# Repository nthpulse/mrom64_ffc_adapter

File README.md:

Adapter board that allows an FFC cable to be used with the MROM64 pin header

See https://nthpulse.net/projects/mrom64_selector_panel/

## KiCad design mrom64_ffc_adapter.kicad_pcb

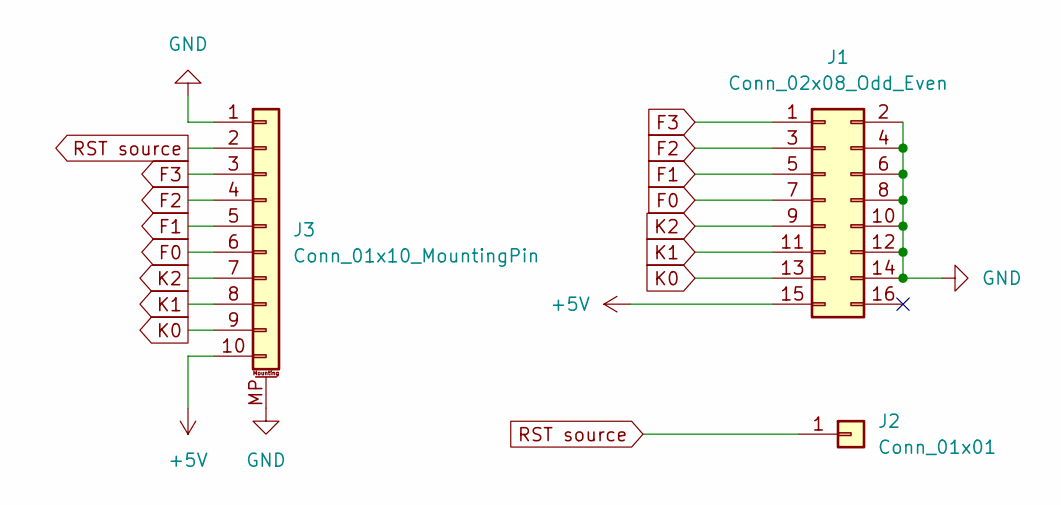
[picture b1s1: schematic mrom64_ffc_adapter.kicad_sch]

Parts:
J1: Conn_02x08_Odd_Even; PinSocket_2x08_P2.54mm_Vertical
J2: Conn_01x01; PinHeader_1x01_P2.54mm_Vertical
J3: Conn_01x10_MountingPin; TE_1-84952-0_1x10-1MP_P1.0mm_Horizontal

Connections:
+5V: J1.15, J3.10
F0: J1.7, J3.6
F1: J1.5, J3.5
F2: J1.3, J3.4
F3: J1.1, J3.3
GND: J1.2, J1.4, J1.6, J1.8, J1.10, J1.12, J1.14, J3.1, J3.MP (MountPin)
K0: J1.13, J3.9
K1: J1.11, J3.8
K2: J1.9, J3.7
RST source: J2.1, J3.2

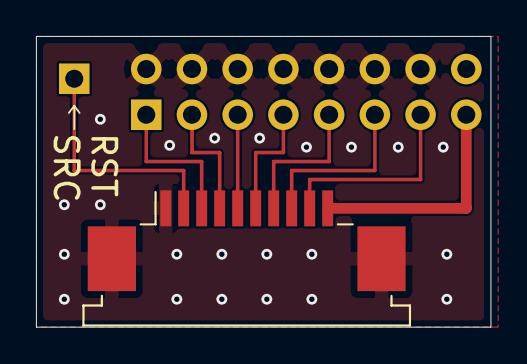
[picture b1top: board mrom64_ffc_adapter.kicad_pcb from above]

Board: 2 copper layers, 25.2 x 16.1 mm, 3 parts (1 on the bottom side), 10 nets.
